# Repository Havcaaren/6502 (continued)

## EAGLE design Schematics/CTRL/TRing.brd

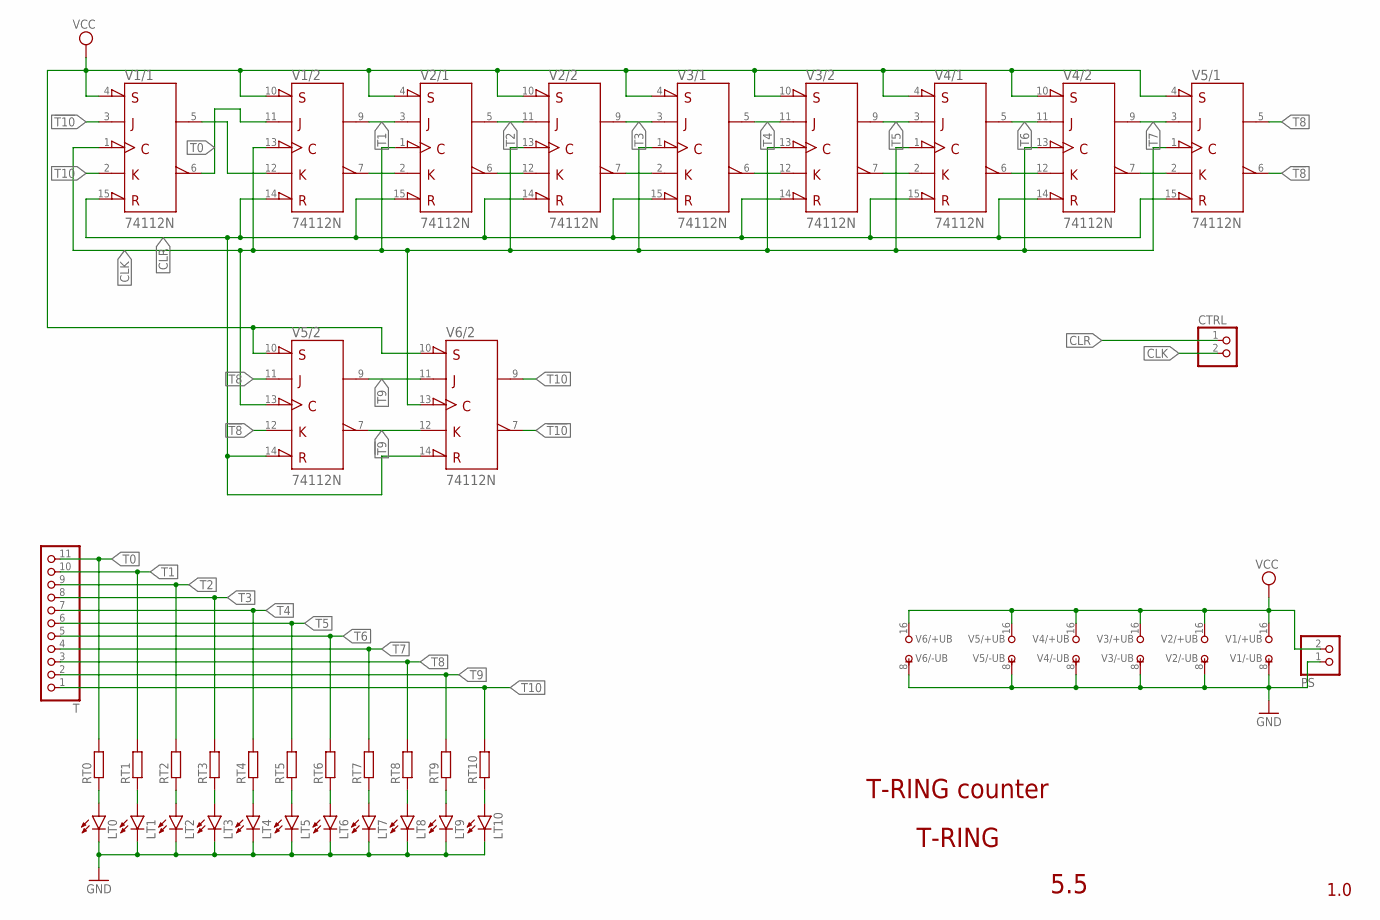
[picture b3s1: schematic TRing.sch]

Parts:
CTRL: PINHD-1X2; 1X02
LT0, LT1, LT2, LT3, LT4, LT5, LT6, LT7, LT8, LT9, LT10: LED5MM
PS: PINHD-1X2; 1X02
RT0, RT1, RT2, RT3, RT4, RT5, RT6, RT7, RT8, RT9, RT10: R-EU_0204/7; 0204/7
T: PINHD-1X11; 1X11
V1, V2, V3, V4, V5, V6: 74112N; DIL16

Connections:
!T8: V5.6 (!Q), V5.12 (K)
!T9: V5.7 (!Q), V6.12 (K)
!T10: V1.3 (J), V6.7 (!Q)
CLK: CTRL.2, V1.1 (CLK), V1.13 (CLK), V2.1 (CLK), V2.13 (CLK), V3.1 (CLK), V3.13 (CLK), V4.1 (CLK), V4.13 (CLK), V5.1 (CLK), V5.13 (CLK), V6.13 (CLK)
CLR: CTRL.1, V1.14 (!CLR), V1.15 (!CLR), V2.14 (!CLR), V2.15 (!CLR), V3.14 (!CLR), V3.15 (!CLR), V4.14 (!CLR), V4.15 (!CLR), V5.14 (!CLR), V5.15 (!CLR), V6.14 (!CLR)
GND: LT0.K (C), LT1.K (C), LT2.K (C), LT3.K (C), LT4.K (C), LT5.K (C), LT6.K (C), LT7.K (C), LT8.K (C), LT9.K (C), LT10.K (C), PS.1, V1.8 (-UB), V2.8 (-UB), V3.8 (-UB), V4.8 (-UB), V5.8 (-UB), V6.8 (-UB)
unnamed: V1.5 (Q), V1.12 (K)
unnamed: LT0.A, RT0.1
unnamed: LT1.A, RT1.1
unnamed: LT2.A, RT2.1
unnamed: V1.7 (!Q), V2.2 (K)
unnamed: LT3.A, RT3.1
unnamed: V2.6 (!Q), V2.12 (K)
unnamed: V2.7 (!Q), V3.2 (K)
unnamed: LT4.A, RT4.1
unnamed: LT5.A, RT5.1
unnamed: LT6.A, RT6.1
unnamed: LT10.A, RT10.1
unnamed: LT7.A, RT7.1
unnamed: V3.6 (!Q), V3.12 (K)
unnamed: V3.7 (!Q), V4.2 (K)
unnamed: LT8.A, RT8.1
unnamed: LT9.A, RT9.1
unnamed: V4.6 (!Q), V4.12 (K)
unnamed: V4.7 (!Q), V5.2 (K)
T0: RT0.2, T.11, V1.6 (!Q), V1.11 (J)
T1: RT1.2, T.10, V1.9 (Q), V2.3 (J)
T2: RT2.2, T.9, V2.5 (Q), V2.11 (J)
T3: RT3.2, T.8, V2.9 (Q), V3.3 (J)
T4: RT4.2, T.7, V3.5 (Q), V3.11 (J)
T5: RT5.2, T.6, V3.9 (Q), V4.3 (J)
T6: RT6.2, T.5, V4.5 (Q), V4.11 (J)
T7: RT7.2, T.4, V4.9 (Q), V5.3 (J)
T8: RT8.2, T.3, V5.5 (Q), V5.11 (J)
T9: RT9.2, T.2, V5.9 (Q), V6.11 (J)
T10: RT10.2, T.1, V1.2 (K), V6.9 (Q)
VCC: PS.2, V1.4 (!PRE), V1.10 (!PRE), V1.16 (+UB), V2.4 (!PRE), V2.10 (!PRE), V2.16 (+UB), V3.4 (!PRE), V3.10 (!PRE), V3.16 (+UB), V4.4 (!PRE), V4.10 (!PRE), V4.16 (+UB), V5.4 (!PRE), V5.10 (!PRE), V5.16 (+UB), V6.10 (!PRE), V6.16 (+UB)

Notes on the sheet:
1.0
5.5
T-RING
T-RING counter

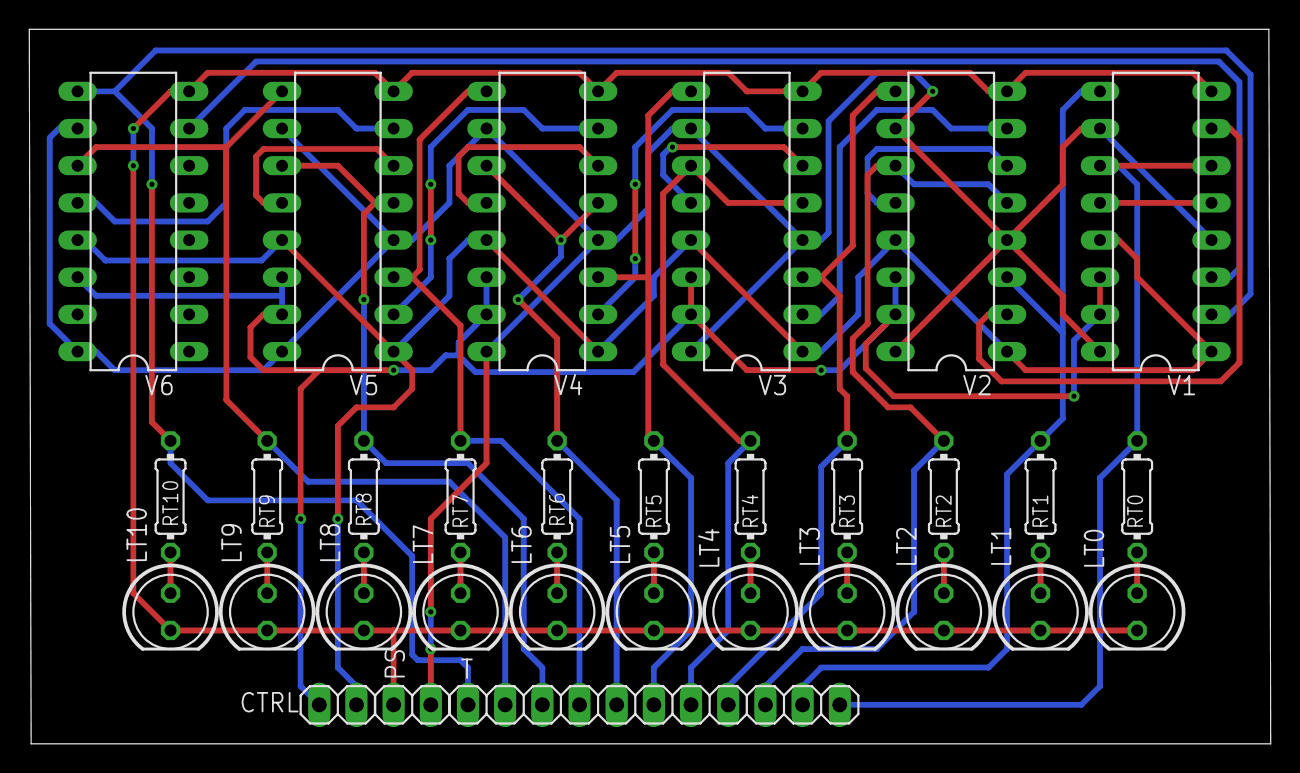
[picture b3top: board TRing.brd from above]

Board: 2 copper layers, 84.8 x 48.8 mm, 31 parts (0 on the bottom side), 37 nets.

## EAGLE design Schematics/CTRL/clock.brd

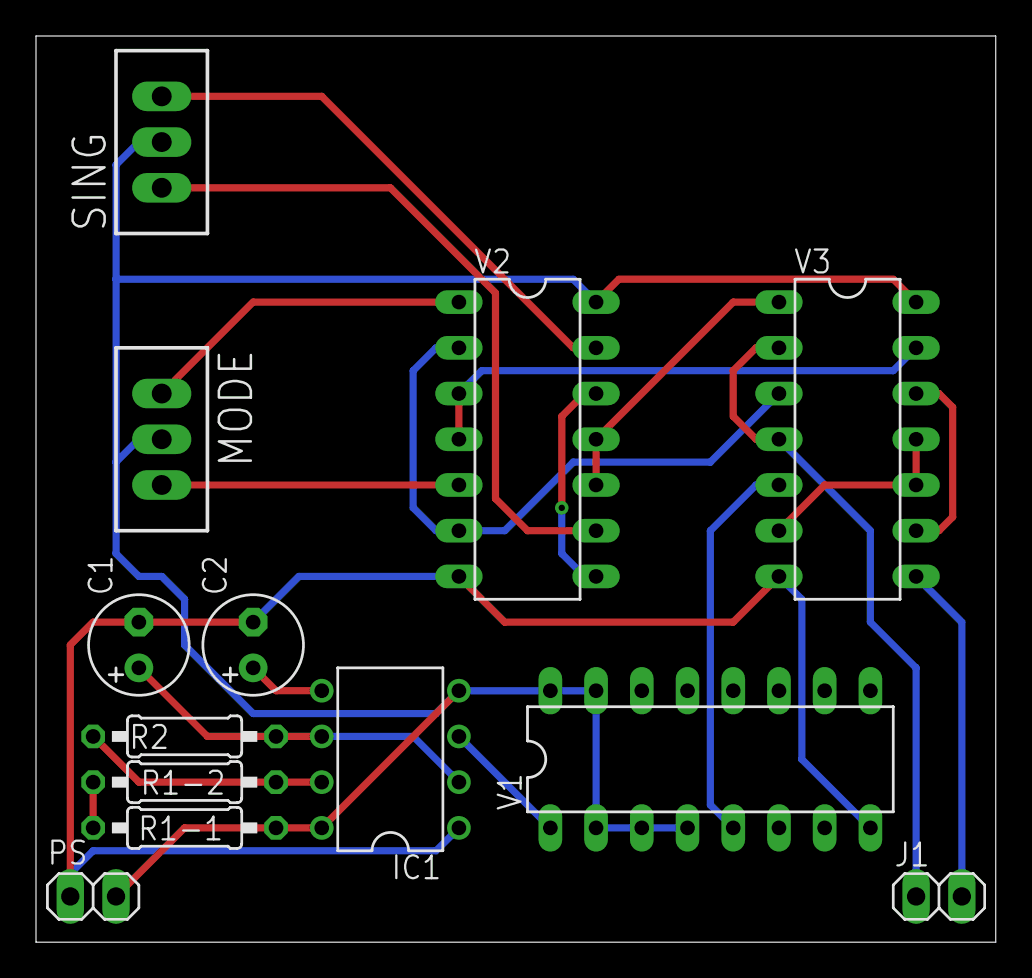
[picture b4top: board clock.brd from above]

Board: 2 copper layers, 53.3 x 50.3 mm, 13 parts (0 on the bottom side), 20 nets.

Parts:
C1, C2: E2,5-6
IC1: NE555N; DIL08
J1: 1X02
MODE: TL32PO; TL3XPO
PS: 1X02
R1-1, R1-2, R2: 0207/10
SING: TL32PO; TL3XPO
V1: 74112N; DIL16
V2: 7400N; DIL14
V3: 7410N; DIL14

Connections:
AUTO: V2.2, V2.6, V3.3
CLK: J1.1, V3.8
CLK-0: IC1.3, V1.1
CLK-1: V1.5, V3.5
GND: C1.-, C2.-, IC1.1, PS.1, V1.8, V2.7, V3.7
HLT: J1.2, V3.2, V3.4
MANUAL: V2.3, V2.4, V3.13
unnamed: C1.+, IC1.2, IC1.6, R2.1
unnamed: IC1.7, R1-2.2, R2.2
unnamed: C2.+, IC1.5
unnamed: R1-1.1, R1-2.1
unnamed: MODE.1, V2.1
unnamed: MODE.3, V2.5
unnamed: SING.1, V2.9
unnamed: SING.3, V2.13
unnamed: V2.8, V2.12
unnamed: V3.6, V3.10, V3.11
unnamed: V3.9, V3.12
SINGLE: V2.10, V2.11, V3.1
VCC: IC1.4, IC1.8, MODE.2, PS.2, R1-1.2, SING.2, V1.2, V1.3, V1.4, V1.15, V1.16, V2.14, V3.14

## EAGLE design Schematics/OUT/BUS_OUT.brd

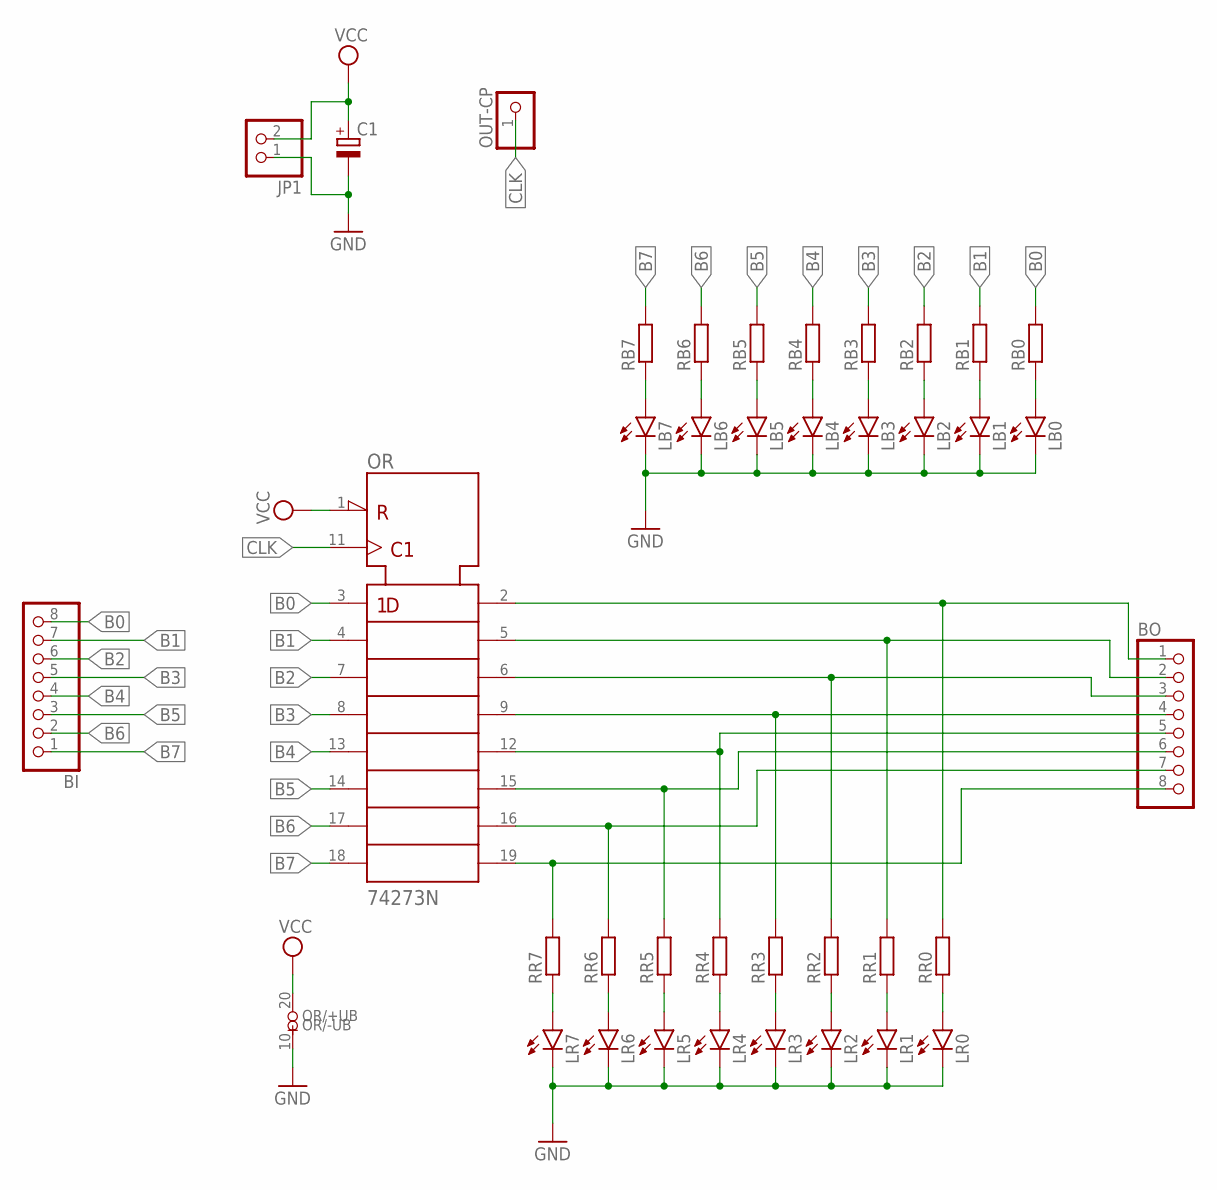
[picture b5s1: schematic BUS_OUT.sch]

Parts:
BI: PINHD-1X8; 1X08
BO: PINHD-1X8; 1X08
C1: CPOL-EUE2.5-6; E2,5-6
JP1: PINHD-1X2; 1X02
LB0, LB1, LB2, LB3, LB4, LB5, LB6, LB7: LED5MM
LR0, LR1, LR2, LR3, LR4, LR5, LR6, LR7: LED5MM
OR: 74273N; DIL20
OUT-CP: PINHD-1X1; 1X01
RB0, RB1, RB2, RB3, RB4, RB5, RB6, RB7: R-EU_0204/7; 0204/7
RR0, RR1, RR2, RR3, RR4, RR5, RR6, RR7: R-EU_0204/7; 0204/7

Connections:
B0: BI.8, OR.3 (1D), RB0.2
B1: BI.7, OR.4 (2D), RB1.2
B2: BI.6, OR.7 (3D), RB2.2
B3: BI.5, OR.8 (4D), RB3.2
B4: BI.4, OR.13 (5D), RB4.2
B5: BI.3, OR.14 (6D), RB5.2
B6: BI.2, OR.17 (7D), RB6.2
B7: BI.1, OR.18 (8D), RB7.2
CLK: OR.11 (CLK), OUT-CP.1
GND: C1.-, JP1.1, LB0.K (C), LB1.K (C), LB2.K (C), LB3.K (C), LB4.K (C), LB5.K (C), LB6.K (C), LB7.K (C), LR0.K (C), LR1.K (C), LR2.K (C), LR3.K (C), LR4.K (C), LR5.K (C), LR6.K (C), LR7.K (C), OR.10 (-UB)
unnamed: LB7.A, RB7.1
unnamed: LB6.A, RB6.1
unnamed: LB5.A, RB5.1
unnamed: LB4.A, RB4.1
unnamed: LR7.A, RR7.1
unnamed: LB3.A, RB3.1
unnamed: BO.8, OR.19 (8Q), RR7.2
unnamed: LR6.A, RR6.1
unnamed: BO.7, OR.16 (7Q), RR6.2
unnamed: LR5.A, RR5.1
unnamed: LB2.A, RB2.1
unnamed: BO.6, OR.15 (6Q), RR5.2
unnamed: LR4.A, RR4.1
unnamed: BO.5, OR.12 (5Q), RR4.2
unnamed: LR3.A, RR3.1
unnamed: LB1.A, RB1.1
unnamed: BO.4, OR.9 (4Q), RR3.2
unnamed: LR2.A, RR2.1
unnamed: BO.3, OR.6 (3Q), RR2.2
unnamed: LR1.A, RR1.1
unnamed: LB0.A, RB0.1
unnamed: BO.2, OR.5 (2Q), RR1.2
unnamed: LR0.A, RR0.1
unnamed: BO.1, OR.2 (1Q), RR0.2
VCC: C1.+, JP1.2, OR.1 (!CLR), OR.20 (+UB)

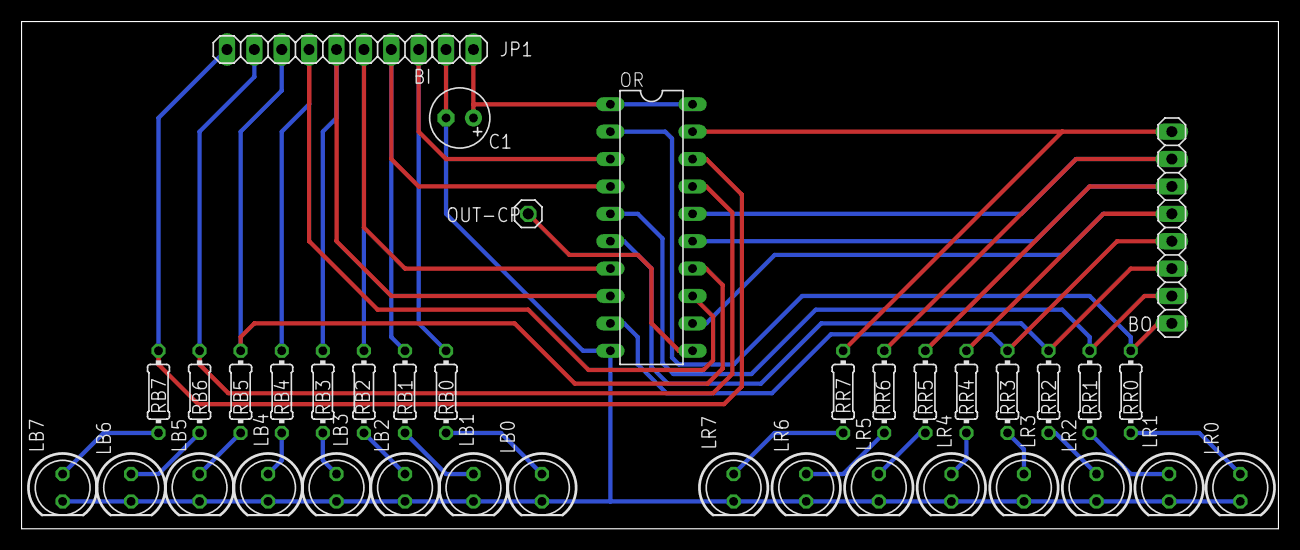
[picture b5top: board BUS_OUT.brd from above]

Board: 2 copper layers, 116.6 x 47.0 mm, 38 parts (0 on the bottom side), 35 nets.

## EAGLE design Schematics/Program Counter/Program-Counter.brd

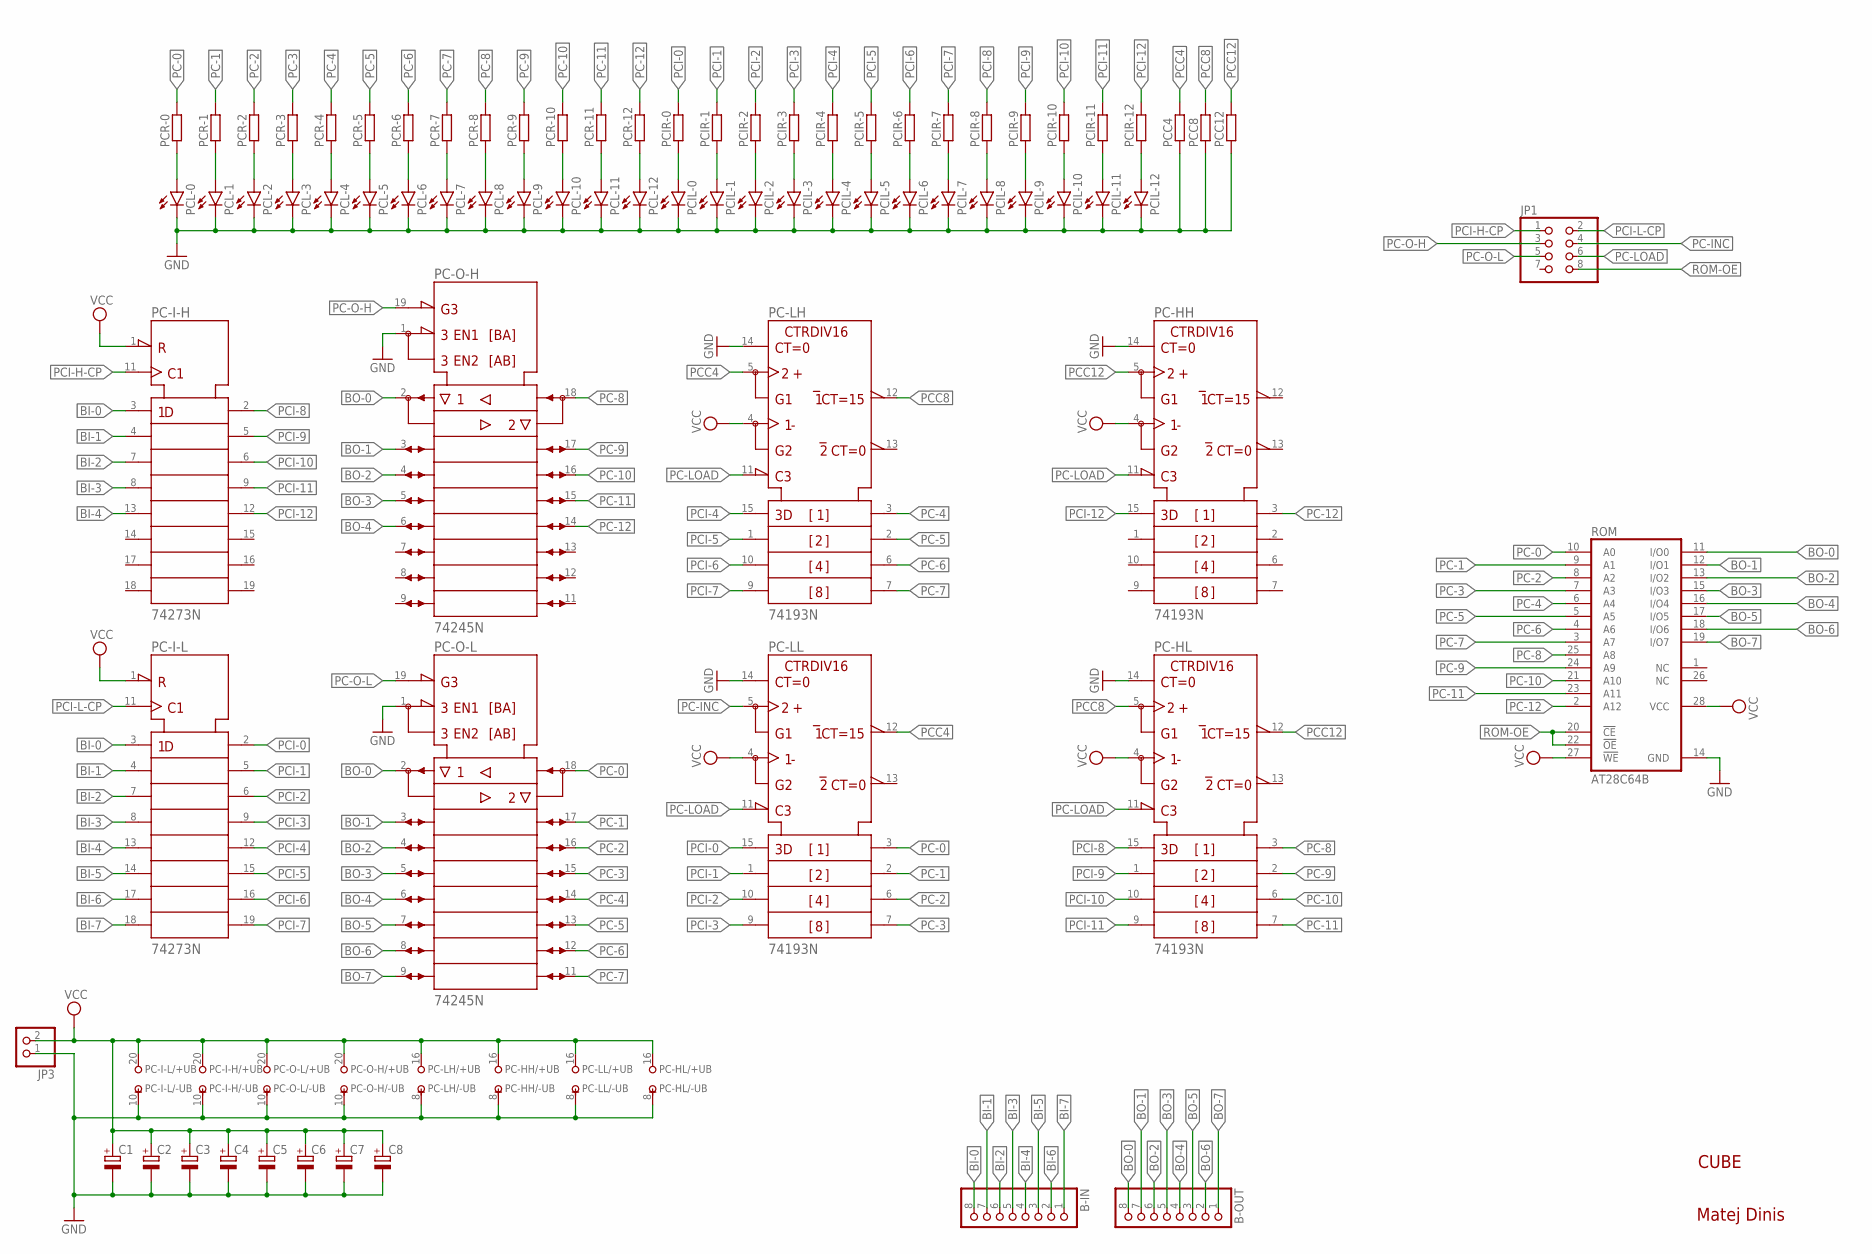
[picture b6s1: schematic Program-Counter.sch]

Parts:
B-IN: PINHD-1X8; 1X08
B-OUT: PINHD-1X8; 1X08
C1, C2, C3, C4, C5, C6, C7, C8: CPOL-EUE3.5-8; E3,5-8
JP1: PINHD-2X4; 2X04
JP3: PINHD-1X2; 1X02
PC-HH: 74193N; DIL16
PC-HL: 74193N; DIL16
PC-I-H: 74273N; DIL20
PC-I-L: 74273N; DIL20
PC-LH: 74193N; DIL16
PC-LL: 74193N; DIL16
PC-O-H: 74245N; DIL20
PC-O-L: 74245N; DIL20
PCC4, PCC8, PCC12: R-EU_0207/10; 0207/10
PCIL-0, PCIL-1, PCIL-2, PCIL-3, PCIL-4, PCIL-5, PCIL-6, PCIL-7, PCIL-8, PCIL-9, PCIL-10, PCIL-11, PCIL-12: LED5MM
PCIR-0, PCIR-1, PCIR-2, PCIR-3, PCIR-4, PCIR-5, PCIR-6, PCIR-7, PCIR-8, PCIR-9, PCIR-10, PCIR-11, PCIR-12: R-EU_0207/10; 0207/10
PCL-0, PCL-1, PCL-2, PCL-3, PCL-4, PCL-5, PCL-6, PCL-7, PCL-8, PCL-9, PCL-10, PCL-11, PCL-12: LED5MM
PCR-0, PCR-1, PCR-2, PCR-3, PCR-4, PCR-5, PCR-6, PCR-7, PCR-8, PCR-9, PCR-10, PCR-11, PCR-12: R-EU_0207/10; 0207/10
ROM: AT28C64B; DIL28-6

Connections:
BI-0: B-IN.8, PC-I-H.3 (1D), PC-I-L.3 (1D)
BI-1: B-IN.7, PC-I-H.4 (2D), PC-I-L.4 (2D)
BI-2: B-IN.6, PC-I-H.7 (3D), PC-I-L.7 (3D)
BI-3: B-IN.5, PC-I-H.8 (4D), PC-I-L.8 (4D)
BI-4: B-IN.4, PC-I-H.13 (5D), PC-I-L.13 (5D)
BI-5: B-IN.3, PC-I-L.14 (6D)
BI-6: B-IN.2, PC-I-L.17 (7D)
BI-7: B-IN.1, PC-I-L.18 (8D)
BO-0: B-OUT.8, PC-O-H.2 (A1), PC-O-L.2 (A1), ROM.11 (I/O0)
BO-1: B-OUT.7, PC-O-H.3 (A2), PC-O-L.3 (A2), ROM.12 (I/O1)
BO-2: B-OUT.6, PC-O-H.4 (A3), PC-O-L.4 (A3), ROM.13 (I/O2)
BO-3: B-OUT.5, PC-O-H.5 (A4), PC-O-L.5 (A4), ROM.15 (I/O3)
BO-4: B-OUT.4, PC-O-H.6 (A5), PC-O-L.6 (A5), ROM.16 (I/O4)
BO-5: B-OUT.3, PC-O-L.7 (A6), ROM.17 (I/O5)
BO-6: B-OUT.2, PC-O-L.8 (A7), ROM.18 (I/O6)
BO-7: B-OUT.1, PC-O-L.9 (A8), ROM.19 (I/O7)
GND: C1.-, C2.-, C3.-, C4.-, C5.-, C6.-, C7.-, C8.-, JP3.1, PC-HH.8 (-UB), PC-HH.14 (CLR), PC-HL.8 (-UB), PC-HL.14 (CLR), PC-I-H.10 (-UB), PC-I-L.10 (-UB), PC-LH.8 (-UB), PC-LH.14 (CLR), PC-LL.8 (-UB), PC-LL.14 (CLR), PC-O-H.1 (DIR), PC-O-H.10 (-UB), PC-O-L.1 (DIR), PC-O-L.10 (-UB), PCC4.1, PCC8.1, PCC12.1, PCIL-0.K (C), PCIL-1.K (C), PCIL-2.K (C), PCIL-3.K (C), PCIL-4.K (C), PCIL-5.K (C), PCIL-6.K (C), PCIL-7.K (C), PCIL-8.K (C), PCIL-9.K (C), PCIL-10.K (C), PCIL-11.K (C), PCIL-12.K (C), PCL-0.K (C), PCL-1.K (C), PCL-2.K (C), PCL-3.K (C), PCL-4.K (C), PCL-5.K (C), PCL-6.K (C), PCL-7.K (C), PCL-8.K (C), PCL-9.K (C), PCL-10.K (C), PCL-11.K (C), PCL-12.K (C), ROM.14 (GND)
unnamed: PCL-0.A, PCR-0.1
unnamed: PCL-1.A, PCR-1.1
unnamed: PCL-2.A, PCR-2.1
unnamed: PCL-3.A, PCR-3.1
unnamed: PCL-4.A, PCR-4.1
unnamed: PCL-5.A, PCR-5.1
unnamed: PCL-6.A, PCR-6.1
unnamed: PCL-7.A, PCR-7.1
unnamed: PCL-8.A, PCR-8.1
unnamed: PCL-9.A, PCR-9.1
unnamed: PCL-10.A, PCR-10.1
unnamed: PCL-11.A, PCR-11.1
unnamed: PCL-12.A, PCR-12.1
unnamed: PCIL-0.A, PCIR-0.1
unnamed: PCIL-1.A, PCIR-1.1
unnamed: PCIL-2.A, PCIR-2.1
unnamed: PCIL-3.A, PCIR-3.1
unnamed: PCIL-4.A, PCIR-4.1
unnamed: PCIL-5.A, PCIR-5.1
unnamed: PCIL-6.A, PCIR-6.1
unnamed: PCIL-7.A, PCIR-7.1
unnamed: PCIL-8.A, PCIR-8.1
unnamed: PCIL-9.A, PCIR-9.1
unnamed: PCIL-10.A, PCIR-10.1
unnamed: PCIL-11.A, PCIR-11.1
unnamed: PCIL-12.A, PCIR-12.1
PC-0: PC-LL.3 (QA), PC-O-L.18 (B1), PCR-0.2, ROM.10 (A0)
PC-1: PC-LL.2 (QB), PC-O-L.17 (B2), PCR-1.2, ROM.9 (A1)
PC-2: PC-LL.6 (QC), PC-O-L.16 (B3), PCR-2.2, ROM.8 (A2)
PC-3: PC-LL.7 (QD), PC-O-L.15 (B4), PCR-3.2, ROM.7 (A3)
PC-4: PC-LH.3 (QA), PC-O-L.14 (B5), PCR-4.2, ROM.6 (A4)
PC-5: PC-LH.2 (QB), PC-O-L.13 (B6), PCR-5.2, ROM.5 (A5)
PC-6: PC-LH.6 (QC), PC-O-L.12 (B7), PCR-6.2, ROM.4 (A6)
PC-7: PC-LH.7 (QD), PC-O-L.11 (B8), PCR-7.2, ROM.3 (A7)
PC-8: PC-HL.3 (QA), PC-O-H.18 (B1), PCR-8.2, ROM.25 (A8)
PC-9: PC-HL.2 (QB), PC-O-H.17 (B2), PCR-9.2, ROM.24 (A9)
PC-10: PC-HL.6 (QC), PC-O-H.16 (B3), PCR-10.2, ROM.21 (A10)
PC-11: PC-HL.7 (QD), PC-O-H.15 (B4), PCR-11.2, ROM.23 (A11)
PC-12: PC-HH.3 (QA), PC-O-H.14 (B5), PCR-12.2, ROM.2 (A12)
PC-INC: JP1.4, PC-LL.5 (UP)
PC-LOAD: JP1.6, PC-HH.11 (!LOAD), PC-HL.11 (!LOAD), PC-LH.11 (!LOAD), PC-LL.11 (!LOAD)
PC-O-H: JP1.3, PC-O-H.19 (!G)
PC-O-L: JP1.5, PC-O-L.19 (!G)
PCC4: PC-LH.5 (UP), PC-LL.12 (!CO), PCC4.2
PCC8: PC-HL.5 (UP), PC-LH.12 (!CO), PCC8.2
PCC12: PC-HH.5 (UP), PC-HL.12 (!CO), PCC12.2
PCI-0: PC-I-L.2 (1Q), PC-LL.15 (A), PCIR-0.2
PCI-1: PC-I-L.5 (2Q), PC-LL.1 (B), PCIR-1.2
PCI-2: PC-I-L.6 (3Q), PC-LL.10 (C), PCIR-2.2
PCI-3: PC-I-L.9 (4Q), PC-LL.9 (D), PCIR-3.2
PCI-4: PC-I-L.12 (5Q), PC-LH.15 (A), PCIR-4.2
PCI-5: PC-I-L.15 (6Q), PC-LH.1 (B), PCIR-5.2
PCI-6: PC-I-L.16 (7Q), PC-LH.10 (C), PCIR-6.2
PCI-7: PC-I-L.19 (8Q), PC-LH.9 (D), PCIR-7.2
PCI-8: PC-HL.15 (A), PC-I-H.2 (1Q), PCIR-8.2
PCI-9: PC-HL.1 (B), PC-I-H.5 (2Q), PCIR-9.2
PCI-10: PC-HL.10 (C), PC-I-H.6 (3Q), PCIR-10.2
PCI-11: PC-HL.9 (D), PC-I-H.9 (4Q), PCIR-11.2
PCI-12: PC-HH.15 (A), PC-I-H.12 (5Q), PCIR-12.2
PCI-H-CP: JP1.1, PC-I-H.11 (CLK)
PCI-L-CP: JP1.2, PC-I-L.11 (CLK)
ROM-OE: JP1.8, ROM.20 (!CE), ROM.22 (!OE)
VCC: C1.+, C2.+, C3.+, C4.+, C5.+, C6.+, C7.+, C8.+, JP3.2, PC-HH.4 (DOWN), PC-HH.16 (+UB), PC-HL.4 (DOWN), PC-HL.16 (+UB), PC-I-H.1 (!CLR), PC-I-H.20 (+UB), PC-I-L.1 (!CLR), PC-I-L.20 (+UB), PC-LH.4 (DOWN), PC-LH.16 (+UB), PC-LL.4 (DOWN), PC-LL.16 (+UB), PC-O-H.20 (+UB), PC-O-L.20 (+UB), ROM.27 (!WE), ROM.28 (VCC)

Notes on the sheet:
CUBE
Matej Dinis

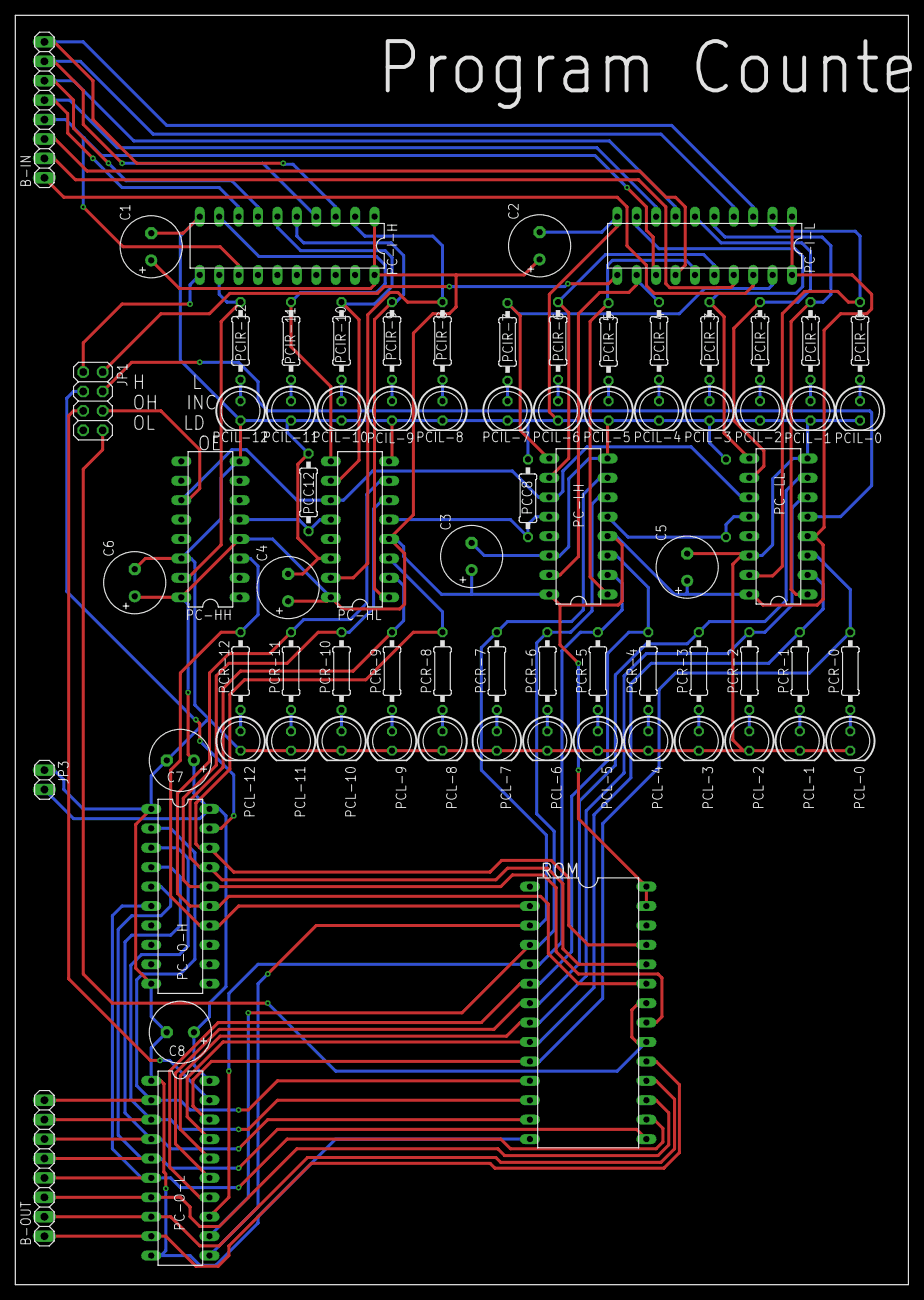
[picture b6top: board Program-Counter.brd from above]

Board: 2 copper layers, 116.8 x 166.0 mm, 76 parts (1 on the bottom side), 80 nets.

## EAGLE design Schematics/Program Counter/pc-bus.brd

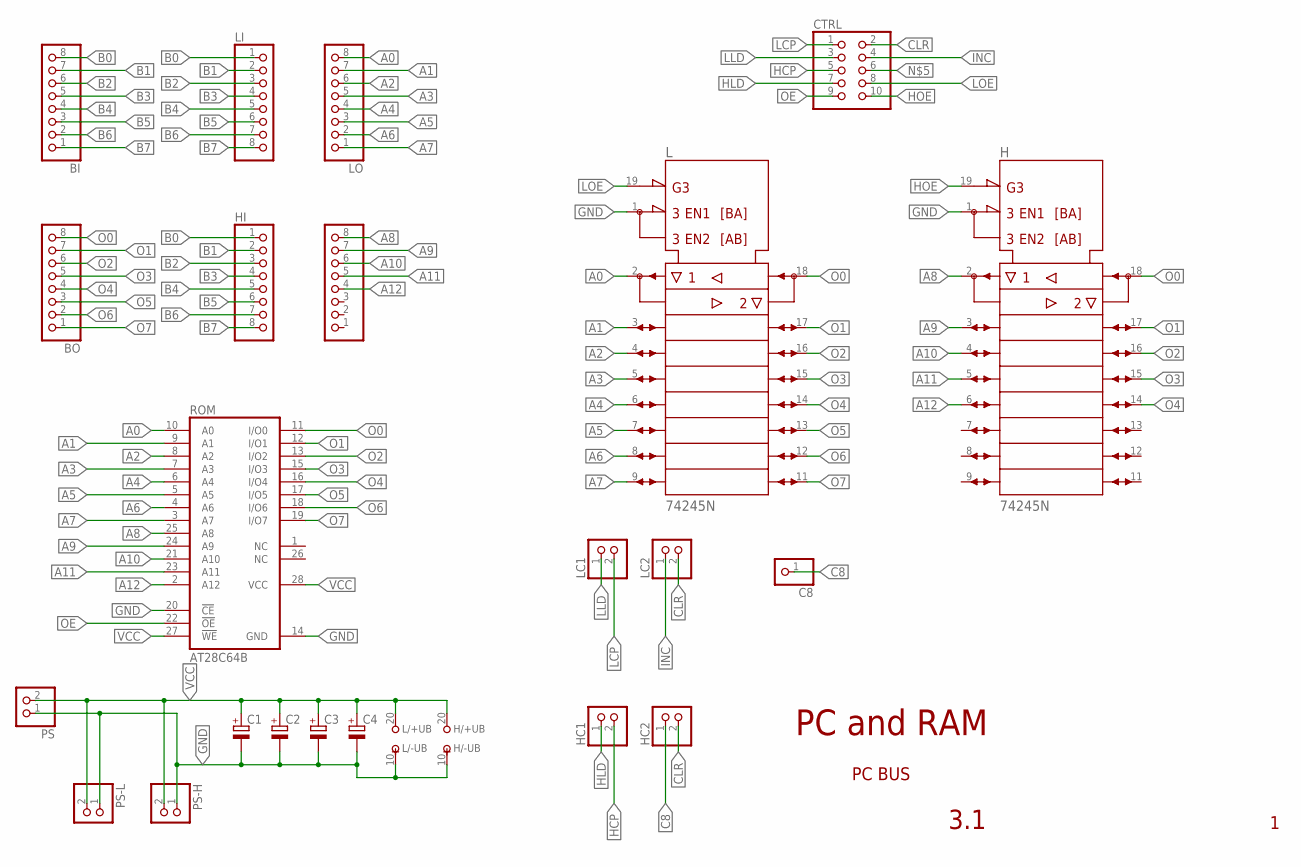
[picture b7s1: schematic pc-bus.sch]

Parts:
BI: PINHD-1X8; 1X08
BO: PINHD-1X8; 1X08
C1, C2, C3, C4: CPOL-EUE2.5-6; E2,5-6
C8: PINHD-1X1; 1X01
CTRL: PINHD-2X5; 2X05
H: 74245N; DIL20
HC1, HC2: PINHD-1X2; 1X02
HI: PINHD-1X8; 1X08
HO: PINHD-1X8; 1X08
L: 74245N; DIL20
LC1, LC2: PINHD-1X2; 1X02
LI: PINHD-1X8; 1X08
LO: PINHD-1X8; 1X08
PS: PINHD-1X2; 1X02
PS-H: PINHD-1X2; 1X02
PS-L: PINHD-1X2; 1X02
ROM: AT28C64B; DIL28-6

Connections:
A0: L.2 (A1), LO.8, ROM.10 (A0)
A1: L.3 (A2), LO.7, ROM.9 (A1)
A2: L.4 (A3), LO.6, ROM.8 (A2)
A3: L.5 (A4), LO.5, ROM.7 (A3)
A4: L.6 (A5), LO.4, ROM.6 (A4)
A5: L.7 (A6), LO.3, ROM.5 (A5)
A6: L.8 (A7), LO.2, ROM.4 (A6)
A7: L.9 (A8), LO.1, ROM.3 (A7)
A8: H.2 (A1), HO.8, ROM.25 (A8)
A9: H.3 (A2), HO.7, ROM.24 (A9)
A10: H.4 (A3), HO.6, ROM.21 (A10)
A11: H.5 (A4), HO.5, ROM.23 (A11)
A12: H.6 (A5), HO.4, ROM.2 (A12)
B0: BI.8, HI.1, LI.1
B1: BI.7, HI.2, LI.2
B2: BI.6, HI.3, LI.3
B3: BI.5, HI.4, LI.4
B4: BI.4, HI.5, LI.5
B5: BI.3, HI.6, LI.6
B6: BI.2, HI.7, LI.7
B7: BI.1, HI.8, LI.8
C8: C8.1, HC2.1
CLR: CTRL.2, HC2.2, LC2.2
GND: C1.-, C2.-, C3.-, C4.-, H.1 (DIR), H.10 (-UB), L.1 (DIR), L.10 (-UB), PS.1, PS-H.1, PS-L.1, ROM.14 (GND), ROM.20 (!CE)
HCP: CTRL.5, HC1.2
HLD: CTRL.7, HC1.1
HOE: CTRL.10, H.19 (!G)
INC: CTRL.4, LC2.1
LCP: CTRL.1, LC1.2
LLD: CTRL.3, LC1.1
LOE: CTRL.8, L.19 (!G)
O0: BO.8, H.18 (B1), L.18 (B1), ROM.11 (I/O0)
O1: BO.7, H.17 (B2), L.17 (B2), ROM.12 (I/O1)
O2: BO.6, H.16 (B3), L.16 (B3), ROM.13 (I/O2)
O3: BO.5, H.15 (B4), L.15 (B4), ROM.15 (I/O3)
O4: BO.4, H.14 (B5), L.14 (B5), ROM.16 (I/O4)
O5: BO.3, L.13 (B6), ROM.17 (I/O5)
O6: BO.2, L.12 (B7), ROM.18 (I/O6)
O7: BO.1, L.11 (B8), ROM.19 (I/O7)
OE: CTRL.9, ROM.22 (!OE)
VCC: C1.+, C2.+, C3.+, C4.+, H.20 (+UB), L.20 (+UB), PS.2, PS-H.2, PS-L.2, ROM.27 (!WE), ROM.28 (VCC)

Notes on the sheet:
PC and RAM
PC BUS
3.1

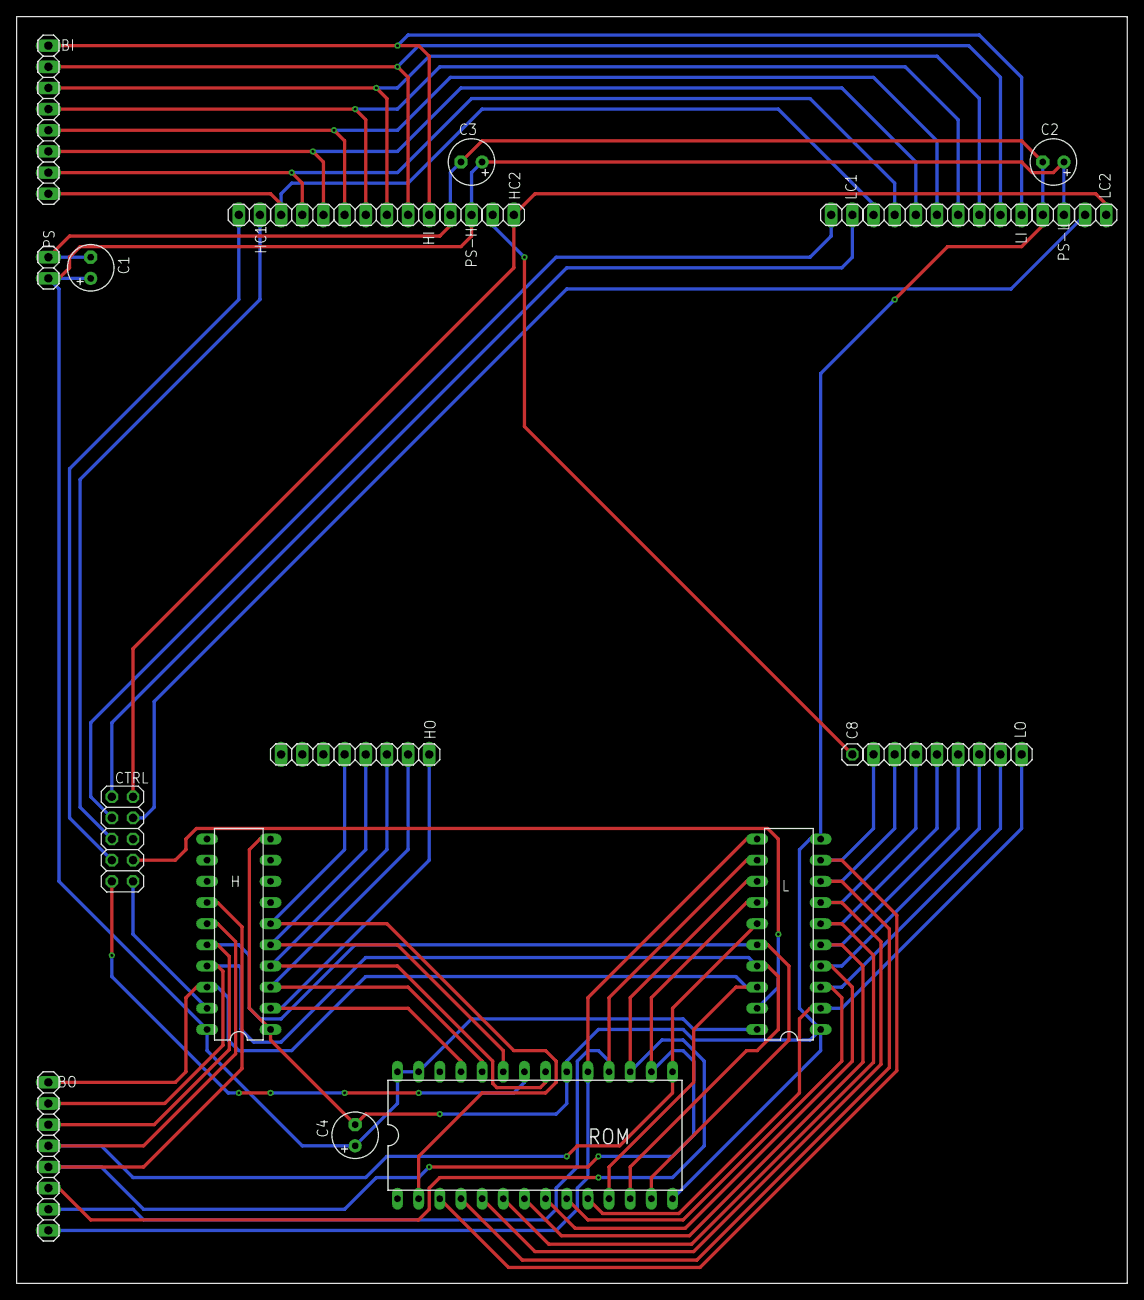
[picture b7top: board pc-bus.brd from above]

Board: 2 copper layers, 133.3 x 152.1 mm, 22 parts (0 on the bottom side), 41 nets.
